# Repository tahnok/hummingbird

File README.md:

```
 _   _ _   _ __  __ __  __ ___ _   _  ____ ____ ___ ____  ____  
| | | | | | |  \/  |  \/  |_ _| \ | |/ ___| __ )_ _|  _ \|  _ \ 
| |_| | | | | |\/| | |\/| || ||  \| | |  _|  _ \| || |_) | | | |
|  _  | |_| | |  | | |  | || || |\  | |_| | |_) | ||  _ <| |_| |
|_| |_|\___/|_|  |_|_|  |_|___|_| \_|\____|____/___|_| \_\____/ 
```

A lightweight device for capture altitude and other data from a kite

**r1 status:** DO NOT PLUG IN A BATTERY

## References

 - BMP388, microSD and Slide switch footprint from Digikey
 - [RFM69 Footprint](https://github.com/benwis/SparkFun-Kicad-Libraries/blob/master/SparkFun-RF.pretty/RFM69HCW-XXXS2.kicad_mod)

## Building

 The `gerbers` folder has a zip file if you want to order your own PCB.

 There is a `bom.csv` that contains all the parts and digikey part numbers you need

 There's also an `interactive_bom.html` that is from the excellent [InteractiveHtmlBom](https://github.com/openscopeproject/InteractiveHtmlBom) plugin

 ## Known Issues

 ### Rev 1

  1. **Battery connector is wired backwards**
  1. microSD footprint is backwards, so it is un-usable
  1. Battery and battery charging to do not work. I plugged one in, immediatly smelled burning. Current theory is that I forgot a current limiting resistor on the LDO's EN pin, so too much current from battery (but not from USB).

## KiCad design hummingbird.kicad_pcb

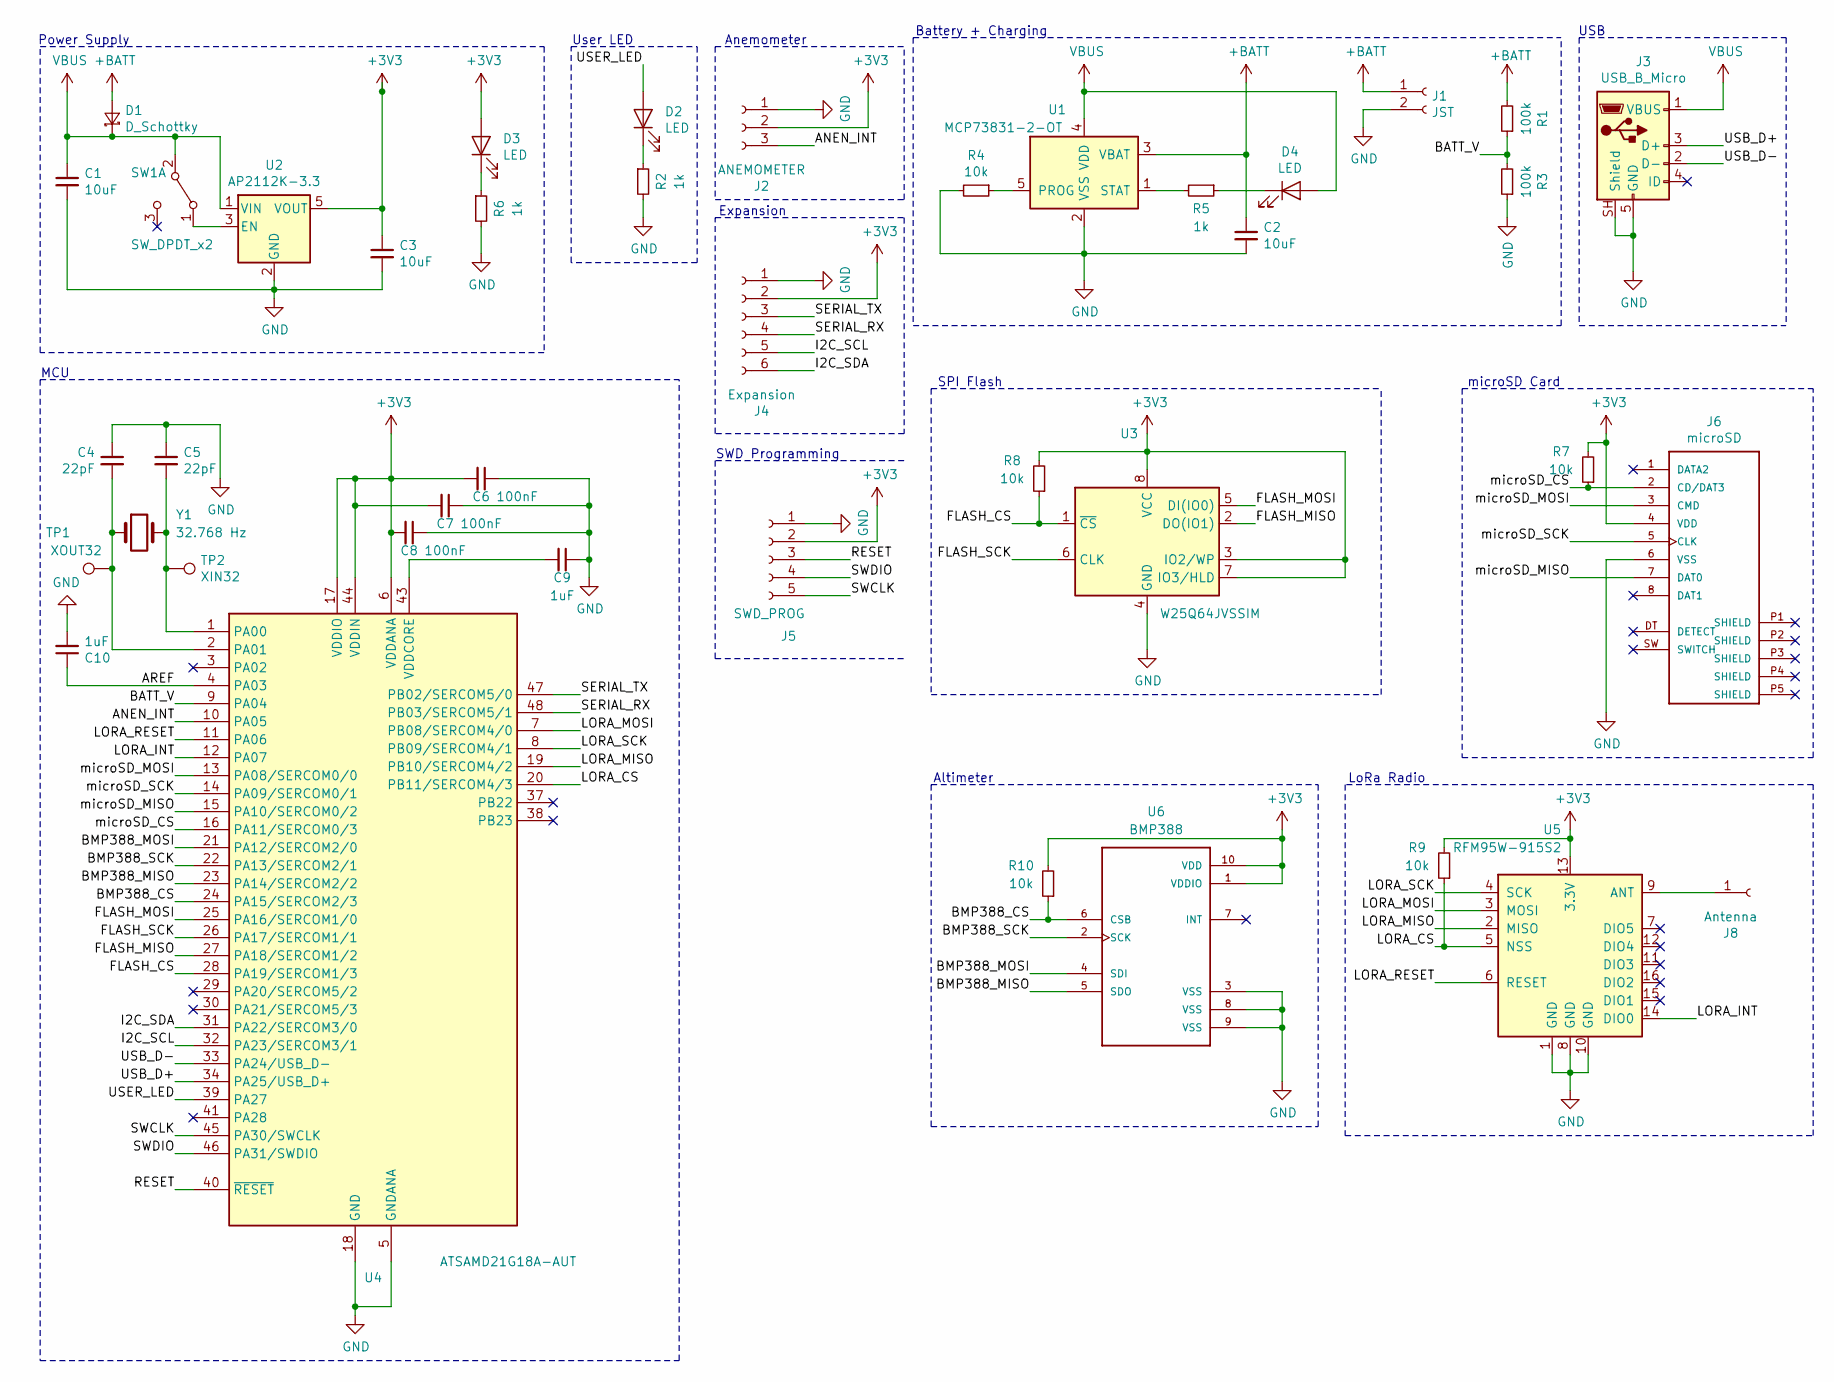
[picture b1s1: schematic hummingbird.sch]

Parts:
C1, C2, C3: 10uF; C_0603_1608Metric; DigiKey Part Number 1276-1119-1-ND
C4, C5: 22pF; C_0603_1608Metric; DigiKey Part Number 478-1167-1-ND
C6, C7, C8: 100nF; C_0603_1608Metric; DigiKey Part Number 311-1088-1-ND
C9, C10: 1uF; C_0603_1608Metric; DigiKey Part Number 1276-1182-1-ND
D1: D_Schottky; D_0603_1608Metric; DigiKey Part Number 478-7798-1-ND
D2, D3, D4: LED; LED_0603_1608Metric; DigiKey Part Number SML-D12U1WT86CT-ND
J1: JST; PinHeader_2x1mm_P2mm_SMD_RA; DigiKey Part Number 455-1749-1-ND
J2: ANEMOMETER; PinSocket_1x03_P2.54mm_Vertical
J3: USB_B_Micro; USB_Micro_B_Female_10118194-0001LF; DigiKey Part Number 609-4618-1-ND
J4: Expansion; PinSocket_1x06_P2.54mm_Vertical
J5: SWD_PROG; PinSocket_1x05_P2.54mm_Vertical
J6: microSD; MOLEX_503182-1852; DigiKey Part Number WM12834CT-ND
J8: Antenna; PinSocket_1x01_P2.54mm_Vertical
R1, R3: 100k; R_0603_1608Metric; DigiKey Part Number RR08P100KDCT-ND
R2, R5, R6: 1k; R_0603_1608Metric; DigiKey Part Number RHM1.0KDCT-ND
R4, R7, R8, R9, R10: 10k; R_0603_1608Metric; DigiKey Part Number RHM10KADCT-ND
SW1: SW_DPDT_x2; Switch_Slide_JS202011SCQN; DigiKey Part Number 401-2002-1-ND
TP1: XOUT32; TestPoint_Pad_D1.0mm
TP2: XIN32; TestPoint_Pad_D1.0mm
U1: MCP73831-2-OT; SOT-23-5; DigiKey Part Number MCP73831T-2ACI/OTCT-ND
U2: AP2112K-3.3; SOT-23-5; DigiKey Part Number AP2112K-3.3TRG1DICT-ND
U3: W25Q64JVSSIM; SOIC-8_5.23x5.23mm_P1.27mm; DigiKey Part Number W25Q64JVSSIMCT-ND
U4: ATSAMD21G18A-AUT; TQFP-48_7x7mm_P0.5mm; DigiKey Part Number ATSAMD21G18A-AUTCT-ND
U5: RFM95W-915S2; RFM69HCW-XXXS2; DigiKey Part Number RFM95W-915S2-ND
U6: BMP388; PQFN50P200X200X80-10N; DigiKey Part Number 828-1079-1-ND
Y1: 32.768 Hz; Crystal_SMD_3215-2Pin_3.2x1.5mm; DigiKey Part Number 535-9542-1-ND

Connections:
+3V3: C3.1, C6.2, C7.2, C8.2, D3.2 (A), J2.2, J4.2, J5.2, J6.4 (VDD), R7.2, R8.2, R9.2, R10.2, U2.5 (VOUT), U3.3 (IO2/WP), U3.7 (IO3/HLD), U3.8 (VCC), U4.6 (VDDANA), U4.17 (VDDIO), U4.36 (VDDIO), U4.44 (VDDIN), U5.13 (3.3V), U6.1 (VDDIO), U6.10 (VDD)
+BATT: C2.1, D1.2 (A), J1.1, R1.2, U1.3 (VBAT)
/ANEN_INT: J2.3, U4.10 (PA05)
/AREF: C10.1, U4.4 (PA03)
/BATT_V: R1.1, R3.2, U4.9 (PA04)
/BMP388_CS: R10.1, U4.24 (PA15/SERCOM2/3), U6.6 (CSB)
/BMP388_MISO: U4.23 (PA14/SERCOM2/2), U6.5 (SDO)
/BMP388_MOSI: U4.21 (PA12/SERCOM2/0), U6.4 (SDI)
/BMP388_SCK: U4.22 (PA13/SERCOM2/1), U6.2 (SCK)
/FLASH_CS: R8.1, U3.1 (~CS), U4.28 (PA19/SERCOM1/3)
/FLASH_MISO: U3.2 (DO(IO1)), U4.27 (PA18/SERCOM1/2)
/FLASH_MOSI: U3.5 (DI(IO0)), U4.25 (PA16/SERCOM1/0)
/FLASH_SCK: U3.6 (CLK), U4.26 (PA17/SERCOM1/1)
/I2C_SCL: J4.5, U4.32 (PA23/SERCOM3/1)
/I2C_SDA: J4.6, U4.31 (PA22/SERCOM3/0)
/LORA_CS: R9.1, U4.20 (PB11/SERCOM4/3), U5.5 (NSS)
/LORA_INT: U4.12 (PA07), U5.14 (DIO0)
/LORA_MISO: U4.19 (PB10/SERCOM4/2), U5.2 (MISO)
/LORA_MOSI: U4.7 (PB08/SERCOM4/0), U5.3 (MOSI)
/LORA_RESET: U4.11 (PA06), U5.6 (RESET)
/LORA_SCK: U4.8 (PB09/SERCOM4/1), U5.4 (SCK)
/RESET: J5.3, U4.40 (~RESET)
/SERIAL_RX: J4.4, U4.48 (PB03/SERCOM5/1)
/SERIAL_TX: J4.3, U4.47 (PB02/SERCOM5/0)
/SWCLK: J5.5, U4.45 (PA30/SWCLK)
/SWDIO: J5.4, U4.46 (PA31/SWDIO)
/USB_D+: J3.3 (D+), U4.34 (PA25/USB_D+)
/USB_D-: J3.2 (D-), U4.33 (PA24/USB_D-)
/USER_LED: D2.2 (A), U4.39 (PA27)
/microSD_CS: J6.2 (CD/DAT3), R7.1, U4.16 (PA11/SERCOM0/3)
/microSD_MISO: J6.7 (DAT0), U4.15 (PA10/SERCOM0/2)
/microSD_MOSI: J6.3 (CMD), U4.13 (PA08/SERCOM0/0)
/microSD_SCK: J6.5 (CLK), U4.14 (PA09/SERCOM0/1)
GND: C1.2, C2.2, C3.2, C4.1, C5.1, C6.1, C7.1, C8.1, C9.1, C10.2, J1.2, J2.1, J3.5 (GND), J3.SH (Shield), J4.1, J5.1, J6.6 (VSS), R2.2, R3.1, R4.2, R6.2, U1.2 (VSS), U2.2 (GND), U3.4 (GND), U4.5 (GNDANA), U4.18 (GND), U4.35 (GND), U4.42 (GND), U5.1 (GND), U5.8 (GND), U5.10 (GND), U6.3 (VSS), U6.8 (VSS), U6.9 (VSS)
unnamed: C4.2, TP1.1, U4.2 (PA01), Y1.1
unnamed: C5.2, TP2.1, U4.1 (PA00), Y1.2
unnamed: C9.2, U4.43 (VDDCORE)
unnamed: D2.1 (K), R2.1
unnamed: D3.1 (K), R6.1
unnamed: D4.1 (K), R5.1
unnamed: J8.1, U5.9 (ANT)
unnamed: R4.1, U1.5 (PROG)
unnamed: R5.2, U1.1 (STAT)
unnamed: SW1.1 (A), U2.3 (EN)
VBUS: C1.1, D1.1 (K), D4.2 (A), J3.1 (VBUS), SW1.2 (B), U1.4 (VDD), U2.1 (VIN)

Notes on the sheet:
Power Supply
Battery + Charging
Altimeter
microSD Card
SPI Flash
LoRa Radio
USB
User LED
Anemometer
Expansion
SWD Programming
MCU

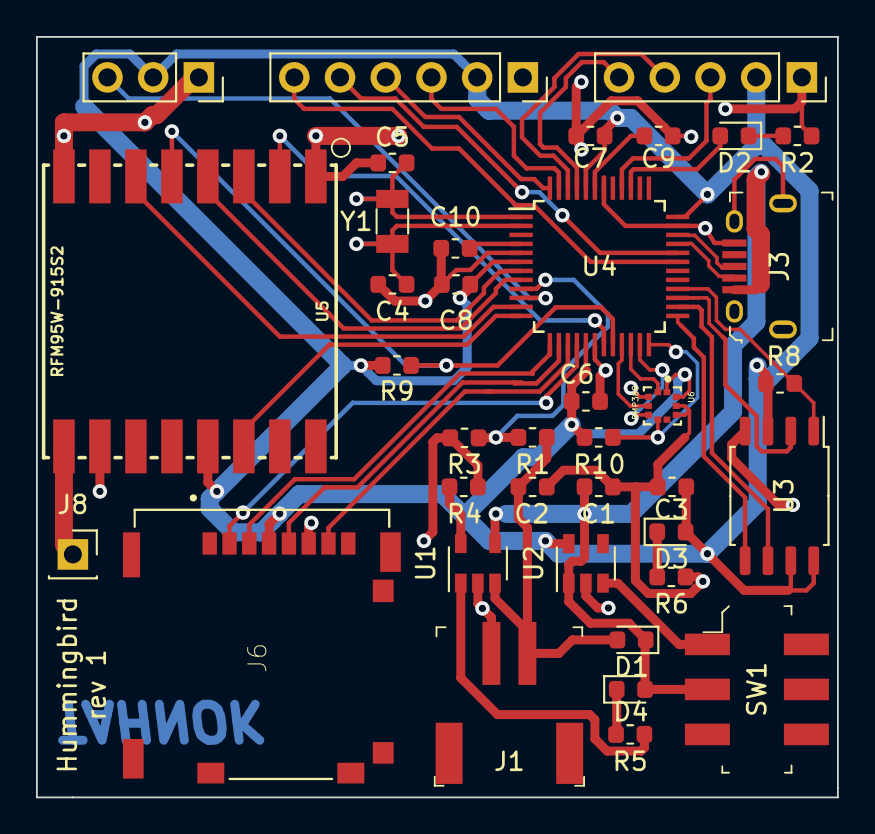
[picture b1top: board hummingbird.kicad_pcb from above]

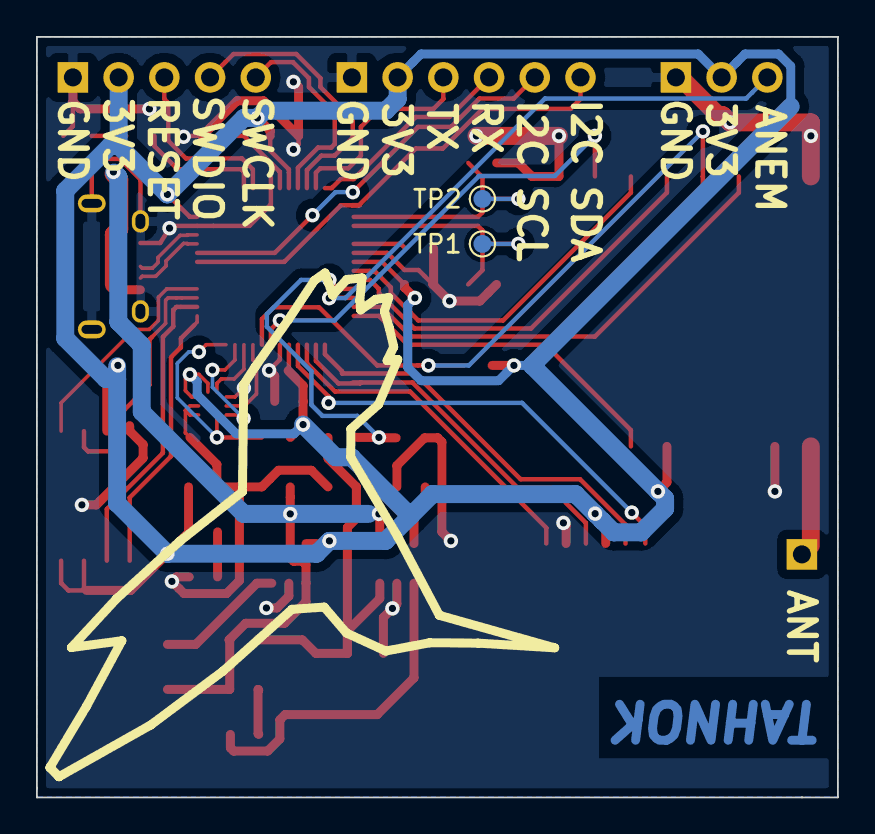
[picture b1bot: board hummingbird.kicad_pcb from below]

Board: 2 copper layers, 44.5 x 42.2 mm, 40 parts (2 on the bottom side), 45 nets.

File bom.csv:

"Item","Qty","Reference(s)","Value","LibPart","Footprint","Datasheet","DigiKey Part Number","Field4","Field5","Field6","Field7","Field8"
"1","3","C1, C2, C3","10uF","Device:C_Small","footprints:C_0603_1608Metric","~","1276-1119-1-ND","","","","",""
"2","2","C4, C5","22pF","Device:C_Small","footprints:C_0603_1608Metric","~","478-1167-1-ND","","","","",""
"3","3","C6, C7, C8","100nF","Device:C_Small","footprints:C_0603_1608Metric","~","311-1088-1-ND","","","","",""
"4","2","C9, C10","1uF","Device:C_Small","footprints:C_0603_1608Metric","~","1276-1182-1-ND","","","","",""
"5","1","D1","D_Schottky","Device:D_Schottky_Small","footprints:D_0603_1608Metric","~","478-7798-1-ND","","","","",""
"6","3","D2, D3, D4","LED","Device:LED","footprints:LED_0603_1608Metric","~","SML-D12U1WT86CT-ND","","","","",""
"7","1","J1","JST","Connector:Conn_01x02_Female","footprints:PinHeader_2x1mm_P2mm_SMD_RA","~","455-1749-1-ND","","","","",""
"8","1","J2","ANEMOMETER","Connector:Conn_01x03_Female","footprints:PinSocket_1x03_P2.54mm_Vertical","~","~","","","","",""
"9","1","J3","USB_B_Micro","symbols:USB_B_Micro","footprints:USB_Micro_B_Female_10118194-0001LF","~","609-4618-1-ND","","","","",""
"10","1","J4","Expansion","Connector:Conn_01x06_Female","footprints:PinSocket_1x06_P2.54mm_Vertical","~","~","","","","",""
"11","1","J5","SWD_PROG","Connector:Conn_01x05_Female","footprints:PinSocket_1x05_P2.54mm_Vertical","~","~","","","","",""
"12","1","J6","microSD","symbols:microSD","microSD_503182-1852:MOLEX_503182-1852","https://www.molex.com/pdm_docs/sd/5031821852_sd.pdf","WM12834CT-ND","MICRO SD NORMAL ULTRALOWPRO8CKTE","Molex","None","WM12834CT-ND","https://www.digikey.com/product-detail/en/molex/5031821852/W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"
"13","1","J7","SOIC_CLIP","Connector:Conn_01x04_Female","footprints:SOIC_clipProgSmall","https://hackaday.io/project/165917-soicbite-programmingdebug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","~","","","","",""
"14","1","J8","Antenna","Connector:Conn_01x01_Female","footprints:PinSocket_1x01_P2.54mm_Vertical","~","","","","","",""
"15","1","J9","Conn_Coaxial","Connector:Conn_Coaxial","footprints:SMA_Molex_73251-1153_EdgeMount_Horizontal"," ~","WM5534-ND","","","","",""
"16","2","R1, R3","100k","Device:R_Small","footprints:R_0603_1608Metric","~","RR08P100KDCT-ND","","","","",""
"17","3","R2, R5, R6","1k","Device:R_Small","footprints:R_0603_1608Metric","~","RHM1.0KDCT-ND","","","","",""
"18","5","R4, R7, R8, R9, R10","10k","Device:R_Small","footprints:R_0603_1608Metric","~","RHM10KADCT-ND","","","","",""
"19","1","SW1","SW_DPDT_x2","Switch:SW_DPDT_x2","footprints:Switch_Slide_JS202011SCQN","","401-2002-1-ND","","","","",""
"20","1","U1","MCP73831-2-OT","Battery_Management:MCP73831-2-OT","footprints:SOT-23-5","http://ww1.microchip.com/downloads/en/DeviceDoc/20001984g.pdf","MCP73831T-2ACI/OTCT-ND","","","","",""
"21","1","U2","AP2112K-3.3","Regulator_Linear:AP2112K-3.3","footprints:SOT-23-5","https://www.diodes.com/assets/Datasheets/AP2112.pdf","AP2112K-3.3TRG1DICT-ND","","","","",""
"22","1","U3","W25Q64JVSSIM","symbols:W25Q64JVSSIM","footprints:SOIC-8_5.23x5.23mm_P1.27mm","http://www.winbond.com/resource-files/w25q64jv%20revj%200327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","W25Q64JVSSIMCT-ND","","","","",""
"23","1","U4","ATSAMD21G18A-AUT","symbols:ATSAMD21G18A-AUT","footprints:TQFP-48_7x7mm_P0.5mm","http://ww1.microchip.com/downloads/en/DeviceDoc/SAMD21-Famil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","ATSAMD21G18A-AUTCT-ND","","","","",""
"24","1","U5","RFM95W-915S2","RF_Module:RFM95W-915S2","footprints:RFM69HCW-XXXS2","https://www.hoperf.com/data/upload/portal/20181127/5bfcbea20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","RFM95W-915S2-ND","","","","",""
"25","1","U6","BMP388","symbols:BMP388","BMP388:PQFN50P200X200X80-10N","https://ae-bst.resource.bosch.com/media/_tech/media/datashee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","828-1079-1-ND","828-1079-1-ND","P-Sensor SPI I2C 1, 25 Bar SMD","https://www.digikey.com/product-detail/en/bosch-sensortec/BM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","BMP388","WFLGA-10 Bosch Tools"
"26","1","Y1","32.768 Hz","Device:Crystal","footprints:Crystal_SMD_3215-2Pin_3.2x1.5mm","https://abracon.com/Resonators/ABS07.pdf","535-9542-1-ND","","","","",""

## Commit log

2019-06-02 start adding wires
2019-06-02 add power, charging and bmp388
2019-06-03 spi flash, lora and microsd added
2019-06-09 add more part datasheets
2019-06-09 add sercom labels, wire up SD card and BMP388
2019-06-09 Add LoRa Spi connections
2019-06-09 finish spi wiring, add connectors
2019-06-13 new voltage regulator, add pullups on CS, fix BMP388 CS
2019-06-14 add crystal and capacitors
2019-06-14 renaming things, add SOIC prog clip header
2019-06-14 schematic first draft
2019-06-14 actually finish schematic and connect pins
2019-06-14 start adding footprints
2019-06-15 add bmp388, SOICbyte and microSD footprint
2019-06-15 finish selecting footprints
2019-06-15 copy all footprints to repo
2019-06-17 Add digikey part numbers
2019-06-17 First attempt at PCB
2019-06-21 remove SMA and some routing
2019-06-22 rough placement (gonna try the autorouter)
2019-06-29 remove SOICbyte, start layout over, rejigger pinouts
2019-07-01 0 unrouted!
2019-07-01 Added labels
2019-07-01 add hummingbird drawing
2019-07-01 move PCB to right file name
2019-07-01 Add schematic rev and date
2019-07-04 add gerbers for r1 production run!
2019-07-04 add bom and interactive bom
2019-07-04 Actual BOM
2019-07-04 prettier readme
2020-02-15 Add known issues section
